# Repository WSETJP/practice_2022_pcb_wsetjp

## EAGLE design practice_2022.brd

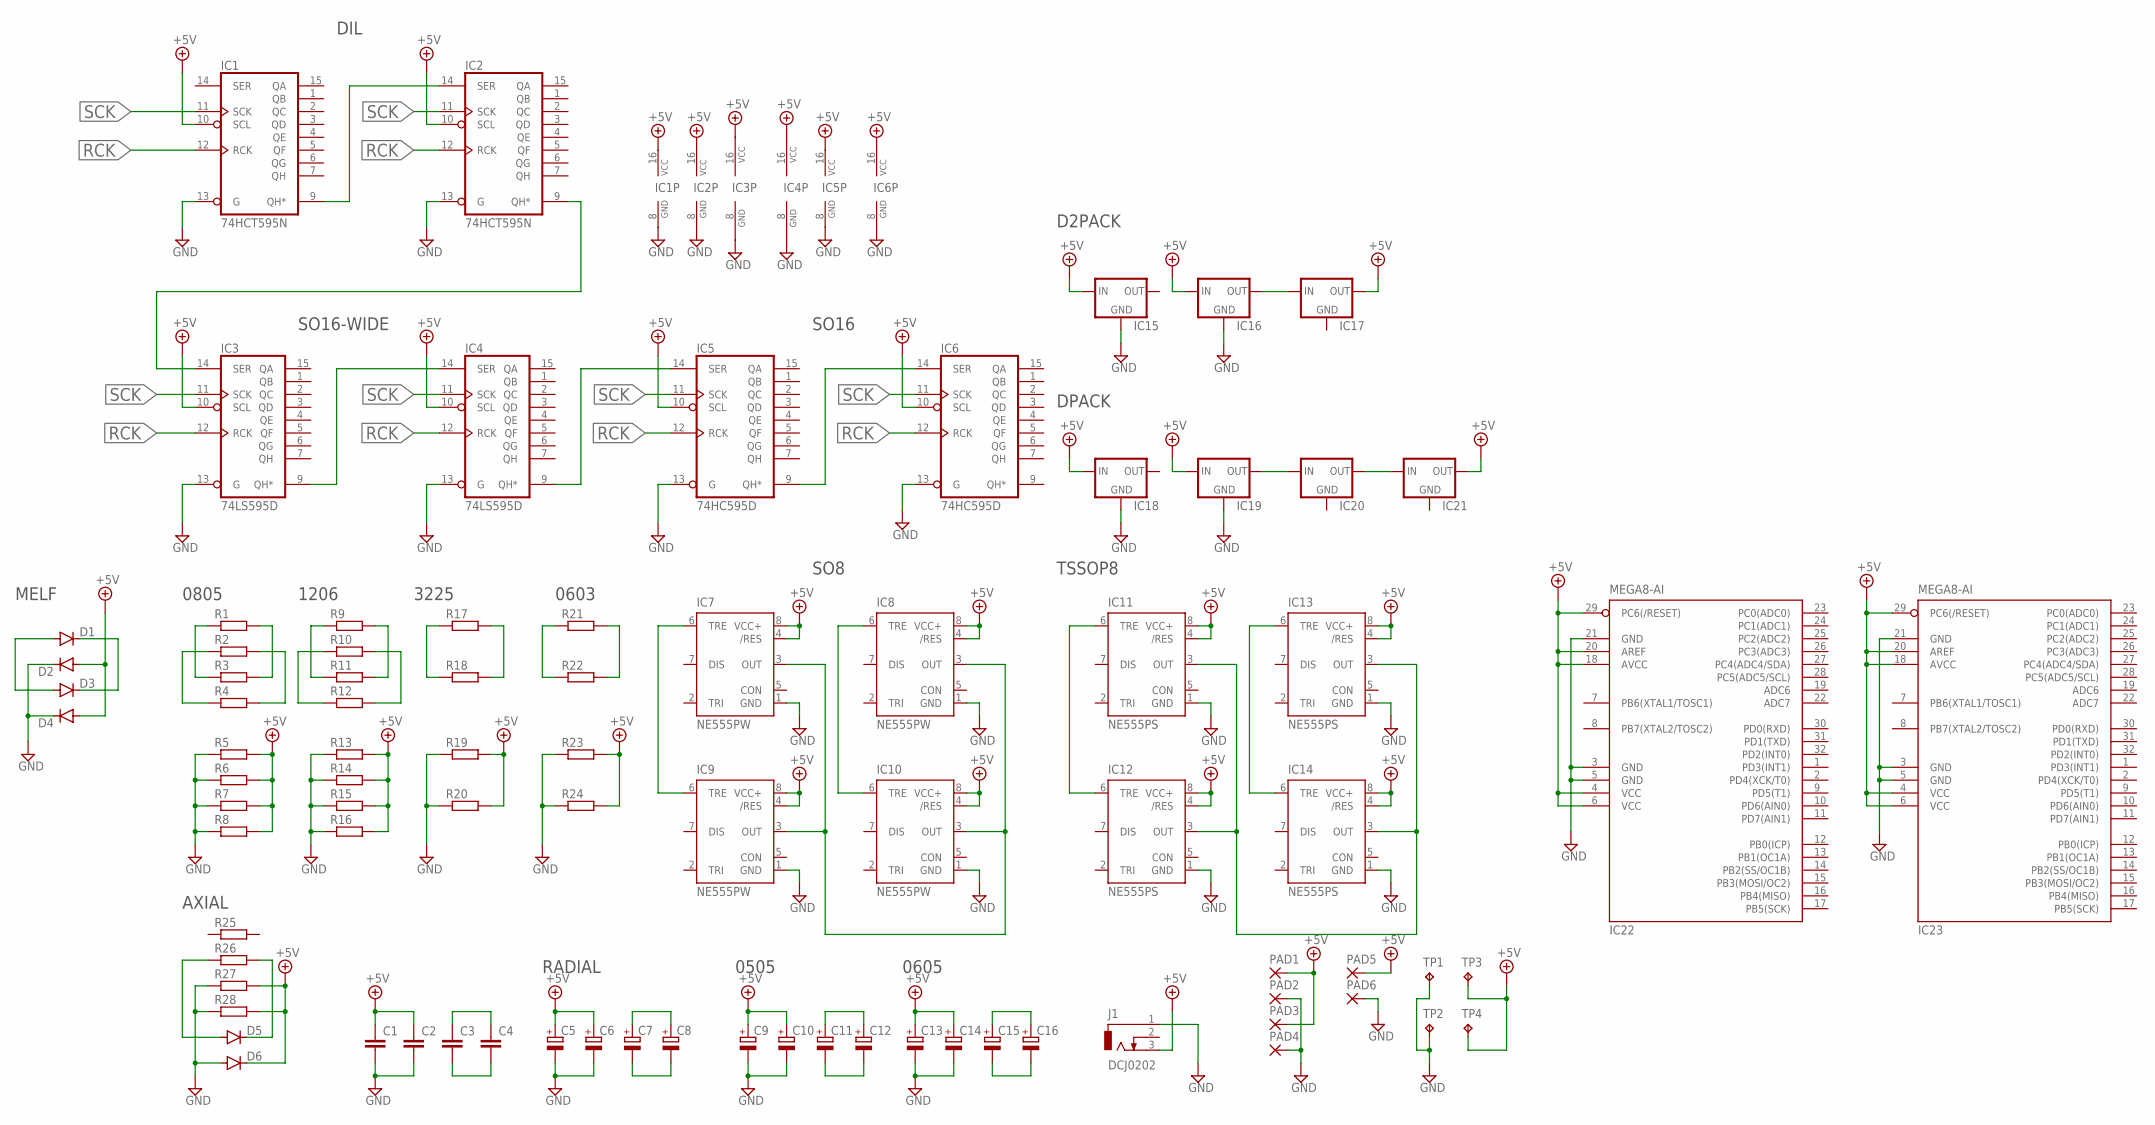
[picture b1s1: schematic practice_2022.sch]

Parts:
C1, C2, C3, C4: C-EU050-024X044; C050-024X044
C5, C6: CPOL-EUE5-4; E5-4
C7, C8: CPOL-EUE2,5-6E; E2,5-6E
C9, C10, C11, C12: CPOL-EU153CLV-0505; 153CLV-0505
C13, C14, C15, C16: CPOL-EU153CLV-0605; 153CLV-0605
D1, D2, D3, D4: DIODE-MINIMELF; MINIMELF
D5, D6: DIODE-DO35-10; DO35-10
IC1, IC2: 74HCT595N; DIL16
IC3, IC4: 74LS595D; SO16
IC5, IC6: 74HC595D; SO16
IC7, IC8, IC9, IC10: NE555PW; TSSOP8
IC11, IC12, IC13, IC14: NE555PS; SO08
IC15, IC16, IC17: 78XX-D2PACK; D2PACK
IC18, IC19, IC20, IC21: 78XX-DPACK; DPACK
IC22, IC23: MEGA8-AI; TQFP32-08
J1: DCJ0202
PAD1, PAD2: SMD2; SMD1,27-2,54
PAD3, PAD4: SMD5; SMD2,54-5,08
PAD5, PAD6: 2,54/1,0
R1, R2, R3, R4, R5, R6, R7, R8: R-EU_R0805; R0805
R9, R10, R11, R12, R13, R14, R15, R16: R-EU_R1206; R1206
R17, R18, R19, R20: R-EU_R3225; R3225
R21, R22, R23, R24: R-EU_R0603; R0603
R25, R26, R27, R28: R-EU_0207/12; 0207/12
TP1, TP2: TPTP20SQ; TP20SQ
TP3, TP4: TPTP06R; TP06R

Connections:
+5V: C1.1, C2.1, C5.+, C6.+, C9.+, C10.+, C13.+, C14.+, D2.A, D4.A, D6.C, IC1.10 (SCL), IC1.16 (VCC), IC2.10 (SCL), IC2.16 (VCC), IC3.10 (SCL), IC3.16 (VCC), IC4.10 (SCL), IC4.16 (VCC), IC5.10 (SCL), IC5.16 (VCC), IC6.10 (SCL), IC6.16 (VCC), IC7.4 (/RES), IC7.8 (VCC+), IC8.4 (/RES), IC8.8 (VCC+), IC9.4 (/RES), IC9.8 (VCC+), IC10.4 (/RES), IC10.8 (VCC+), IC11.4 (/RES), IC11.8 (VCC+), IC12.4 (/RES), IC12.8 (VCC+), IC13.4 (/RES), IC13.8 (VCC+), IC14.4 (/RES), IC14.8 (VCC+), IC15.1 (IN), IC16.1 (IN), IC17.3 (OUT), IC18.1 (IN), IC19.1 (IN), IC21.3 (OUT), IC22.4 (VCC), IC22.6 (VCC), IC22.18 (AVCC), IC22.20 (AREF), IC22.29 (PC6(/RESET)), IC23.4 (VCC), IC23.6 (VCC), IC23.18 (AVCC), IC23.20 (AREF), IC23.29 (PC6(/RESET)), J1.3, PAD1.1, PAD3.1, PAD5.1, R5.2, R6.2, R7.2, R8.2, R13.2, R14.2, R15.2, R16.2, R19.2, R20.2, R23.2, R24.2, R27.2, R28.2, TP3.TP, TP4.TP
GND: C1.2, C2.2, C5.-, C6.-, C9.-, C10.-, C13.-, C14.-, D2.C, D4.C, D6.A, IC1.8 (GND), IC1.13 (G), IC2.8 (GND), IC2.13 (G), IC3.8 (GND), IC3.13 (G), IC4.8 (GND), IC4.13 (G), IC5.8 (GND), IC5.13 (G), IC6.8 (GND), IC6.13 (G), IC7.1 (GND), IC8.1 (GND), IC9.1 (GND), IC10.1 (GND), IC11.1 (GND), IC12.1 (GND), IC13.1 (GND), IC14.1 (GND), IC15.2 (GND), IC16.2 (GND), IC18.4 (GND), IC19.4 (GND), IC22.3 (GND), IC22.5 (GND), IC22.21 (GND), IC23.3 (GND), IC23.5 (GND), IC23.21 (GND), J1.1, PAD2.1, PAD4.1, PAD6.1, R5.1, R6.1, R7.1, R8.1, R13.1, R14.1, R15.1, R16.1, R19.1, R20.1, R23.1, R24.1, R27.1, R28.1, TP1.TP, TP2.TP
unnamed: IC1.9 (QH*), IC2.14 (SER)
unnamed: R1.2, R3.2
unnamed: IC4.9 (QH*), IC5.14 (SER)
unnamed: IC5.9 (QH*), IC6.14 (SER)
unnamed: IC2.9 (QH*), IC3.14 (SER)
unnamed: IC3.9 (QH*), IC4.14 (SER)
unnamed: R1.1, R3.1
unnamed: R2.1, R4.1
unnamed: R2.2, R4.2
unnamed: R9.1, R11.1
unnamed: R10.1, R12.1
unnamed: R9.2, R11.2
unnamed: R10.2, R12.2
unnamed: R17.1, R18.1
unnamed: R17.2, R18.2
unnamed: R21.1, R22.1
unnamed: R21.2, R22.2
unnamed: IC7.3 (OUT), IC8.3 (OUT), IC9.3 (OUT), IC10.3 (OUT)
unnamed: IC7.6 (TRE), IC9.6 (TRE)
unnamed: IC8.6 (TRE), IC10.6 (TRE)
unnamed: IC11.3 (OUT), IC12.3 (OUT), IC13.3 (OUT), IC14.3 (OUT)
unnamed: IC11.6 (TRE), IC12.6 (TRE)
unnamed: D1.A, D3.A
unnamed: D1.C, D3.C
unnamed: IC13.6 (TRE), IC14.6 (TRE)
unnamed: IC16.3 (OUT), IC17.1 (IN)
unnamed: IC19.3 (OUT), IC20.1 (IN)
unnamed: IC20.3 (OUT), IC21.1 (IN)
unnamed: D5.A, R26.1
unnamed: D5.C, R26.2
unnamed: C3.2, C4.2
unnamed: C3.1, C4.1
unnamed: C7.+, C8.+
unnamed: C7.-, C8.-
unnamed: C11.+, C12.+
unnamed: C11.-, C12.-
unnamed: C15.+, C16.+
unnamed: C15.-, C16.-
RCK: IC1.12 (RCK), IC2.12 (RCK), IC3.12 (RCK), IC4.12 (RCK), IC5.12 (RCK), IC6.12 (RCK)
SCK: IC1.11 (SCK), IC2.11 (SCK), IC3.11 (SCK), IC4.11 (SCK), IC5.11 (SCK), IC6.11 (SCK)

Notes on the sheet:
DIL
SO16
SO16-WIDE
0805
1206
3225
0603
MELF
SO8
TSSOP8
D2PACK
DPACK
0505
0605
RADIAL
AXIAL

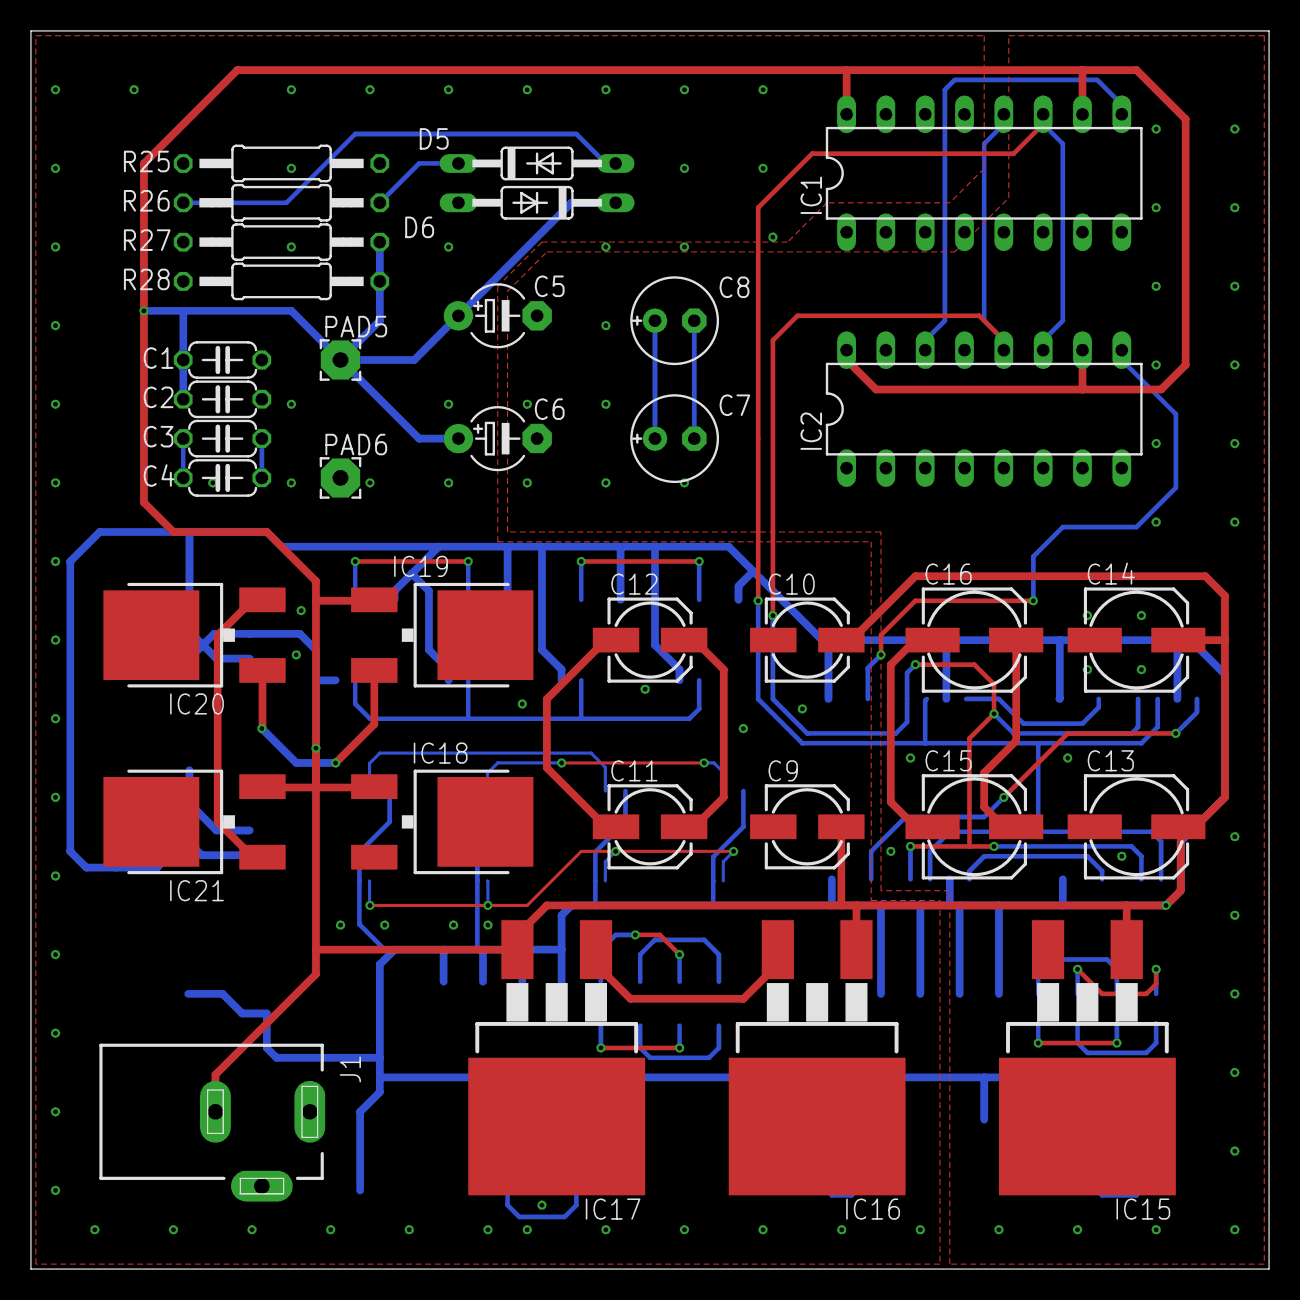
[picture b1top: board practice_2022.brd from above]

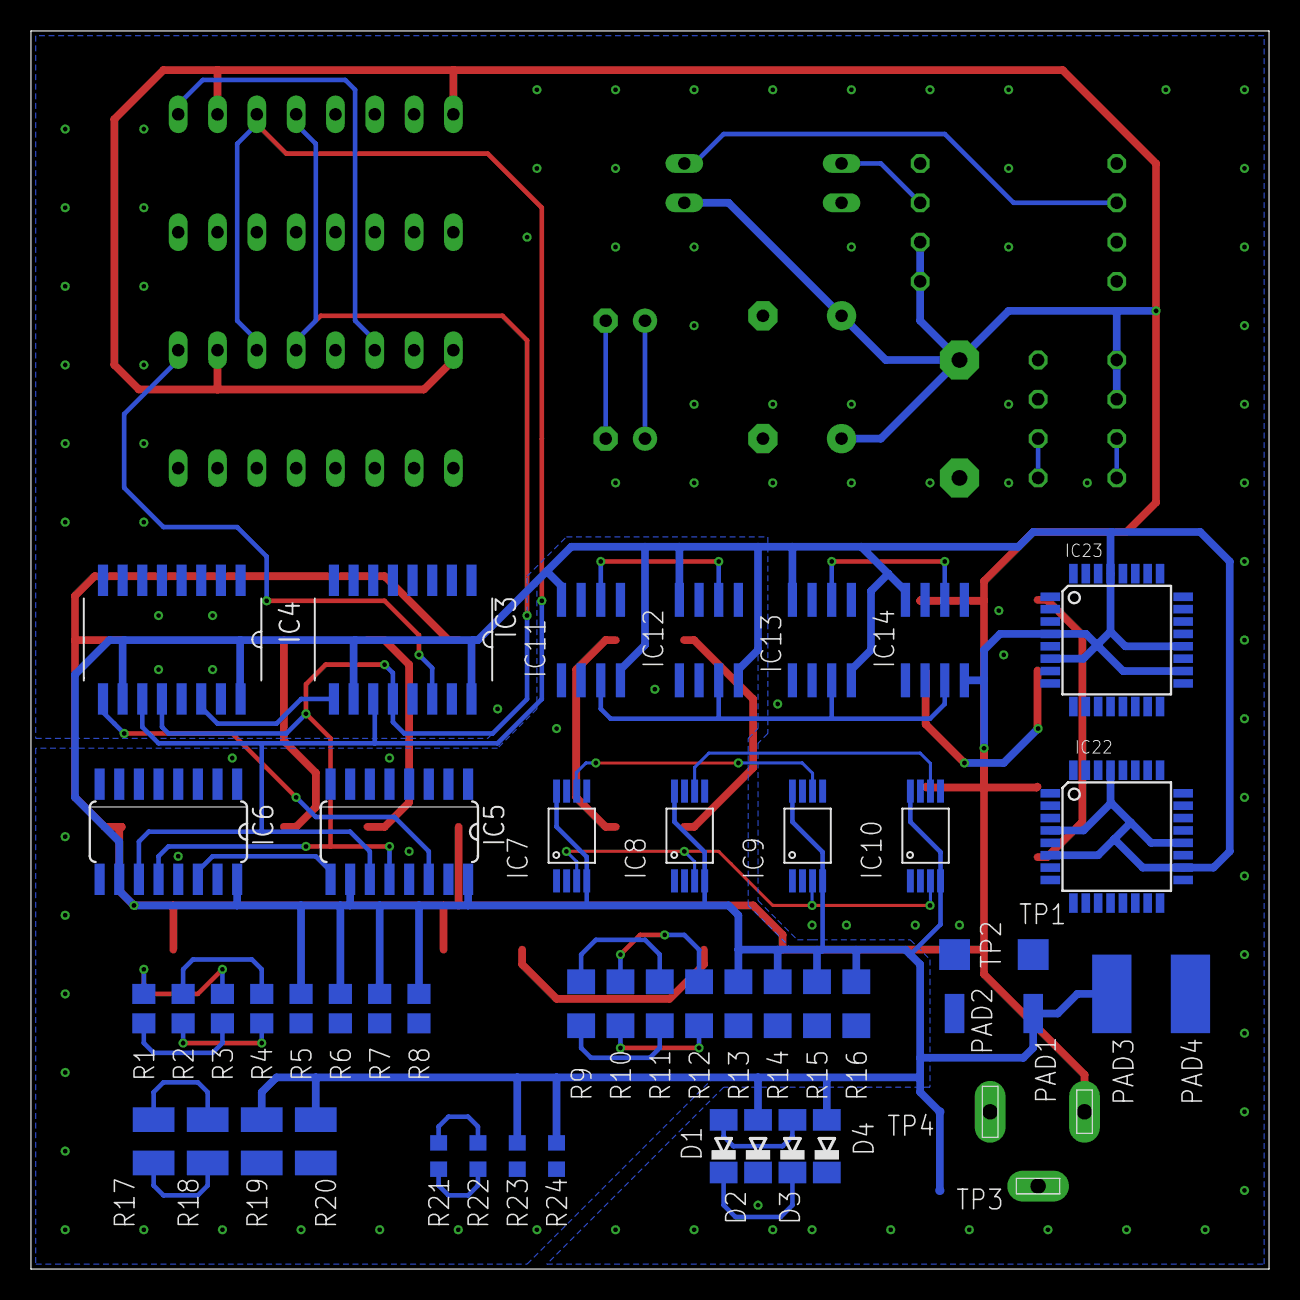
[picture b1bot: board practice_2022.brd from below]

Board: 2 copper layers, 80.0 x 80.0 mm, 84 parts (50 on the bottom side), 42 nets.
